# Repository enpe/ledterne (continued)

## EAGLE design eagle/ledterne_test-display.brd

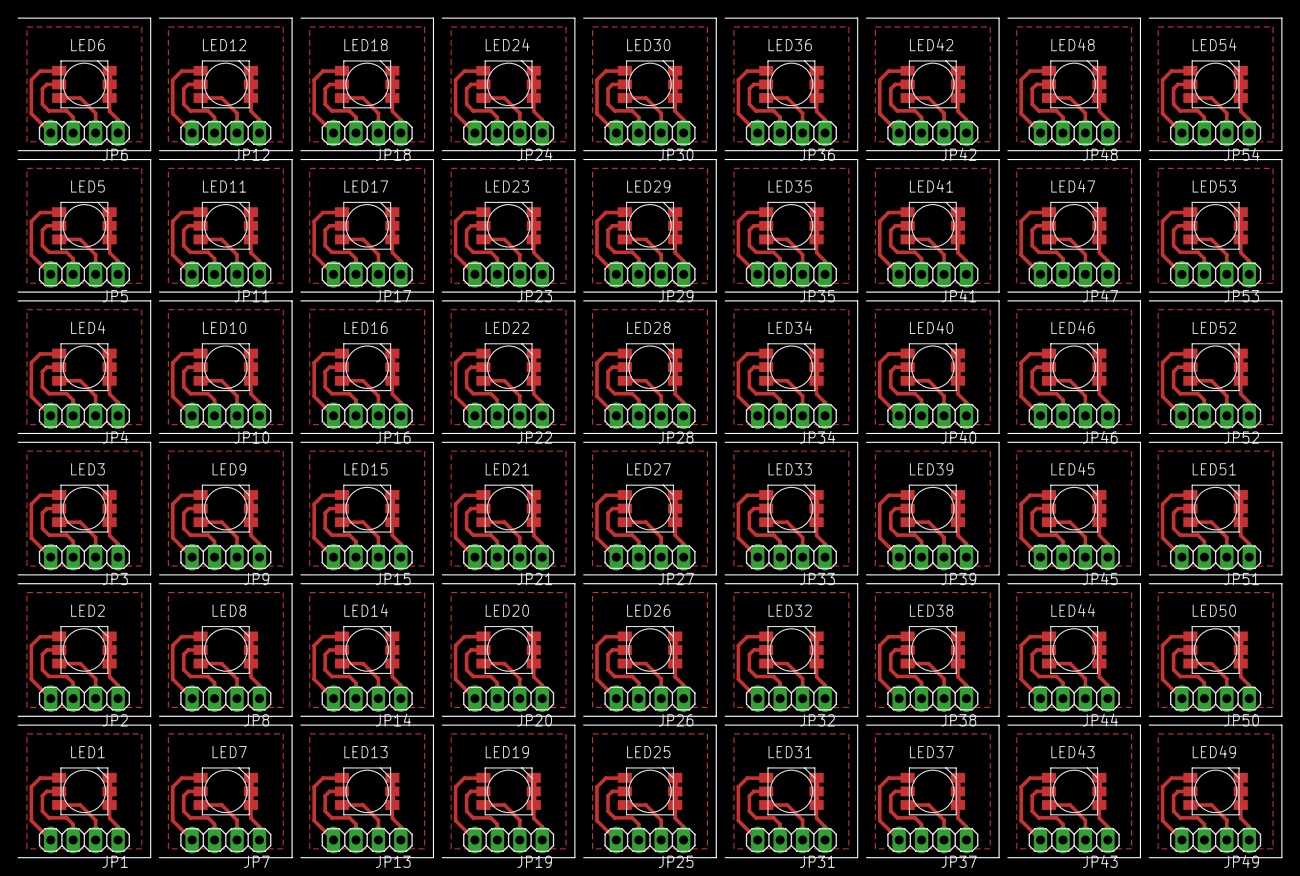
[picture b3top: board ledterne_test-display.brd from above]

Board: 2 copper layers, 143.0 x 95.0 mm, 108 parts (0 on the bottom side), 216 nets.

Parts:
JP1, JP2, JP3, JP4, JP5, JP6, JP7, JP8, JP9, JP10, JP11, JP12, JP13, JP14, JP15, JP16, JP17, JP18, JP19, JP20, JP21, JP22, JP23, JP24, JP25, JP26, JP27, JP28, JP29, JP30, JP31, JP32, JP33, JP34, JP35, JP36, JP37, JP38, JP39, JP40, JP41, JP42, JP43, JP44, JP45, JP46, JP47, JP48, JP49, JP50, JP51, JP52, JP53, JP54: 1X04
LED1, LED2, LED3, LED4, LED5, LED6, LED7, LED8, LED9, LED10, LED11, LED12, LED13, LED14, LED15, LED16, LED17, LED18, LED19, LED20, LED21, LED22, LED23, LED24, LED25, LED26, LED27, LED28, LED29, LED30, LED31, LED32, LED33, LED34, LED35, LED36, LED37, LED38, LED39, LED40, LED41, LED42, LED43, LED44, LED45, LED46, LED47, LED48, LED49, LED50, LED51, LED52, LED53, LED54: RGB-5252; SMD_5252

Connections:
GND: JP1.1, LED1.P1, LED1.P2, LED1.P3
GND1: JP2.1, LED2.P1, LED2.P2, LED2.P3
GND2: JP3.1, LED3.P1, LED3.P2, LED3.P3
GND3: JP4.1, LED4.P1, LED4.P2, LED4.P3
GND4: JP5.1, LED5.P1, LED5.P2, LED5.P3
GND5: JP6.1, LED6.P1, LED6.P2, LED6.P3
GND6: JP7.1, LED7.P1, LED7.P2, LED7.P3
GND7: JP8.1, LED8.P1, LED8.P2, LED8.P3
GND8: JP9.1, LED9.P1, LED9.P2, LED9.P3
GND9: JP10.1, LED10.P1, LED10.P2, LED10.P3
GND10: JP11.1, LED11.P1, LED11.P2, LED11.P3
GND11: JP12.1, LED12.P1, LED12.P2, LED12.P3
GND12: JP13.1, LED13.P1, LED13.P2, LED13.P3
GND13: JP14.1, LED14.P1, LED14.P2, LED14.P3
GND14: JP15.1, LED15.P1, LED15.P2, LED15.P3
GND15: JP16.1, LED16.P1, LED16.P2, LED16.P3
GND16: JP17.1, LED17.P1, LED17.P2, LED17.P3
GND17: JP18.1, LED18.P1, LED18.P2, LED18.P3
GND18: JP19.1, LED19.P1, LED19.P2, LED19.P3
GND19: JP20.1, LED20.P1, LED20.P2, LED20.P3
GND20: JP21.1, LED21.P1, LED21.P2, LED21.P3
GND21: JP22.1, LED22.P1, LED22.P2, LED22.P3
GND22: JP23.1, LED23.P1, LED23.P2, LED23.P3
GND23: JP24.1, LED24.P1, LED24.P2, LED24.P3
GND24: JP25.1, LED25.P1, LED25.P2, LED25.P3
GND25: JP26.1, LED26.P1, LED26.P2, LED26.P3
GND26: JP27.1, LED27.P1, LED27.P2, LED27.P3
GND27: JP28.1, LED28.P1, LED28.P2, LED28.P3
GND28: JP29.1, LED29.P1, LED29.P2, LED29.P3
GND29: JP30.1, LED30.P1, LED30.P2, LED30.P3
GND30: JP31.1, LED31.P1, LED31.P2, LED31.P3
GND31: JP32.1, LED32.P1, LED32.P2, LED32.P3
GND32: JP33.1, LED33.P1, LED33.P2, LED33.P3
GND33: JP34.1, LED34.P1, LED34.P2, LED34.P3
GND34: JP35.1, LED35.P1, LED35.P2, LED35.P3
GND35: JP36.1, LED36.P1, LED36.P2, LED36.P3
GND36: JP37.1, LED37.P1, LED37.P2, LED37.P3
GND37: JP38.1, LED38.P1, LED38.P2, LED38.P3
GND38: JP39.1, LED39.P1, LED39.P2, LED39.P3
GND39: JP40.1, LED40.P1, LED40.P2, LED40.P3
GND40: JP41.1, LED41.P1, LED41.P2, LED41.P3
GND41: JP42.1, LED42.P1, LED42.P2, LED42.P3
GND42: JP43.1, LED43.P1, LED43.P2, LED43.P3
GND43: JP44.1, LED44.P1, LED44.P2, LED44.P3
GND44: JP45.1, LED45.P1, LED45.P2, LED45.P3
GND45: JP46.1, LED46.P1, LED46.P2, LED46.P3
GND46: JP47.1, LED47.P1, LED47.P2, LED47.P3
GND47: JP48.1, LED48.P1, LED48.P2, LED48.P3
GND48: JP49.1, LED49.P1, LED49.P2, LED49.P3
GND49: JP50.1, LED50.P1, LED50.P2, LED50.P3
GND50: JP51.1, LED51.P1, LED51.P2, LED51.P3
GND51: JP52.1, LED52.P1, LED52.P2, LED52.P3
GND52: JP53.1, LED53.P1, LED53.P2, LED53.P3
GND53: JP54.1, LED54.P1, LED54.P2, LED54.P3
unnamed: JP2.2, LED2.P4
unnamed: JP2.3, LED2.P5
unnamed: JP1.2, LED1.P4
unnamed: JP1.3, LED1.P5
unnamed: JP1.4, LED1.P6
unnamed: JP2.4, LED2.P6
unnamed: JP3.2, LED3.P4
unnamed: JP3.3, LED3.P5
unnamed: JP3.4, LED3.P6
unnamed: JP4.2, LED4.P4
unnamed: JP4.3, LED4.P5
unnamed: JP4.4, LED4.P6
unnamed: JP5.2, LED5.P4
unnamed: JP5.3, LED5.P5
unnamed: JP5.4, LED5.P6
unnamed: JP6.2, LED6.P4
unnamed: JP6.3, LED6.P5
unnamed: JP6.4, LED6.P6
unnamed: JP7.2, LED7.P4
unnamed: JP7.3, LED7.P5
unnamed: JP7.4, LED7.P6
unnamed: JP8.2, LED8.P4
unnamed: JP8.3, LED8.P5
unnamed: JP8.4, LED8.P6
unnamed: JP9.2, LED9.P4
unnamed: JP9.3, LED9.P5
unnamed: JP9.4, LED9.P6
unnamed: JP10.2, LED10.P4
unnamed: JP10.3, LED10.P5
unnamed: JP10.4, LED10.P6
unnamed: JP11.2, LED11.P4
unnamed: JP11.3, LED11.P5
unnamed: JP11.4, LED11.P6
unnamed: JP12.2, LED12.P4
unnamed: JP12.3, LED12.P5
unnamed: JP12.4, LED12.P6
unnamed: JP13.2, LED13.P4
unnamed: JP13.3, LED13.P5
unnamed: JP13.4, LED13.P6
unnamed: JP14.2, LED14.P4
unnamed: JP14.3, LED14.P5
unnamed: JP14.4, LED14.P6
unnamed: JP15.2, LED15.P4
unnamed: JP15.3, LED15.P5
unnamed: JP15.4, LED15.P6
unnamed: JP16.2, LED16.P4
unnamed: JP16.3, LED16.P5
unnamed: JP16.4, LED16.P6
unnamed: JP17.2, LED17.P4
unnamed: JP17.3, LED17.P5
unnamed: JP17.4, LED17.P6
unnamed: JP18.2, LED18.P4
unnamed: JP18.3, LED18.P5
unnamed: JP18.4, LED18.P6
unnamed: JP19.2, LED19.P4
unnamed: JP19.3, LED19.P5
unnamed: JP19.4, LED19.P6
unnamed: JP20.2, LED20.P4
unnamed: JP20.3, LED20.P5
unnamed: JP20.4, LED20.P6
unnamed: JP21.2, LED21.P4
unnamed: JP21.3, LED21.P5
unnamed: JP21.4, LED21.P6
unnamed: JP22.2, LED22.P4
unnamed: JP22.3, LED22.P5
unnamed: JP22.4, LED22.P6
unnamed: JP23.2, LED23.P4
unnamed: JP23.3, LED23.P5
unnamed: JP23.4, LED23.P6
unnamed: JP24.2, LED24.P4
unnamed: JP24.3, LED24.P5
unnamed: JP24.4, LED24.P6
unnamed: JP25.2, LED25.P4
unnamed: JP25.3, LED25.P5
unnamed: JP25.4, LED25.P6
unnamed: JP26.2, LED26.P4
unnamed: JP26.3, LED26.P5
unnamed: JP26.4, LED26.P6
unnamed: JP27.2, LED27.P4
unnamed: JP27.3, LED27.P5
unnamed: JP27.4, LED27.P6
unnamed: JP28.2, LED28.P4
unnamed: JP28.3, LED28.P5
unnamed: JP28.4, LED28.P6
unnamed: JP29.2, LED29.P4
unnamed: JP29.3, LED29.P5
unnamed: JP29.4, LED29.P6
unnamed: JP30.2, LED30.P4
unnamed: JP30.3, LED30.P5
unnamed: JP30.4, LED30.P6
unnamed: JP31.2, LED31.P4
unnamed: JP31.3, LED31.P5
unnamed: JP31.4, LED31.P6
unnamed: JP32.2, LED32.P4
unnamed: JP32.3, LED32.P5
unnamed: JP32.4, LED32.P6
unnamed: JP33.2, LED33.P4
unnamed: JP33.3, LED33.P5
unnamed: JP33.4, LED33.P6
unnamed: JP34.2, LED34.P4
unnamed: JP34.3, LED34.P5
unnamed: JP34.4, LED34.P6
unnamed: JP35.2, LED35.P4
unnamed: JP35.3, LED35.P5
unnamed: JP35.4, LED35.P6
unnamed: JP36.2, LED36.P4
unnamed: JP36.3, LED36.P5
unnamed: JP36.4, LED36.P6
unnamed: JP37.2, LED37.P4
unnamed: JP37.3, LED37.P5
unnamed: JP37.4, LED37.P6
unnamed: JP38.2, LED38.P4
unnamed: JP38.3, LED38.P5
unnamed: JP38.4, LED38.P6
unnamed: JP39.2, LED39.P4
unnamed: JP39.3, LED39.P5
unnamed: JP39.4, LED39.P6
unnamed: JP40.2, LED40.P4
unnamed: JP40.3, LED40.P5
unnamed: JP40.4, LED40.P6
unnamed: JP41.2, LED41.P4
unnamed: JP41.3, LED41.P5
unnamed: JP41.4, LED41.P6
unnamed: JP42.2, LED42.P4
unnamed: JP42.3, LED42.P5
unnamed: JP42.4, LED42.P6
unnamed: JP43.2, LED43.P4
unnamed: JP43.3, LED43.P5
unnamed: JP43.4, LED43.P6
unnamed: JP44.2, LED44.P4
unnamed: JP44.3, LED44.P5
unnamed: JP44.4, LED44.P6
unnamed: JP45.2, LED45.P4
unnamed: JP45.3, LED45.P5
unnamed: JP45.4, LED45.P6
unnamed: JP46.2, LED46.P4
unnamed: JP46.3, LED46.P5
unnamed: JP46.4, LED46.P6
unnamed: JP47.2, LED47.P4
unnamed: JP47.3, LED47.P5
unnamed: JP47.4, LED47.P6
unnamed: JP48.2, LED48.P4
unnamed: JP48.3, LED48.P5
unnamed: JP48.4, LED48.P6
unnamed: JP49.2, LED49.P4
unnamed: JP49.3, LED49.P5
unnamed: JP49.4, LED49.P6
unnamed: JP50.2, LED50.P4
unnamed: JP50.3, LED50.P5
unnamed: JP50.4, LED50.P6
unnamed: JP51.2, LED51.P4
unnamed: JP51.3, LED51.P5
unnamed: JP51.4, LED51.P6
unnamed: JP52.2, LED52.P4
unnamed: JP52.3, LED52.P5
unnamed: JP52.4, LED52.P6
unnamed: JP53.2, LED53.P4
unnamed: JP53.3, LED53.P5
unnamed: JP53.4, LED53.P6
unnamed: JP54.2, LED54.P4
unnamed: JP54.3, LED54.P5
unnamed: JP54.4, LED54.P6

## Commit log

2015-07-12 Added a README-file.
2015-07-13 Add some documentation
2015-07-13 Replace ramp up/down hack
    Instead of building the up/down motion into the lookup table,
    the animation is now completely done in the function that
    controls the LED brightness values.
2015-07-13 Fix typo in comments
2015-07-13 Replace busy wait with interrupt-driven frame tick
    Every frame tick advances the color animation one step.
    The 16-bit timer that was previously used for the PWM is now
    replaced by an 8-bit timer. The 16-bit timer is instead used for
    generating the frame tick. This was necessary because the
    required compare values for the frame tick timer would not fit
    into an 8-bit register.
2015-07-18 Add support for 4 more RGB LED outputs
    All 5 LEDs currently show the same colors even though separate
    control of every single LED is already possible in the code.
2015-07-18 Add some TODOs
2015-07-19 Make ramp functions reusable
    The maximum value is not hard-coded anymore.
    The functions also reside in a separate file now. This will
    hopefully prevent clutter in the main program file.
2015-07-19 Refactor up/down ramp animation into object function
    This releases the caller from handling internal implementation
    details (in this case: the variable that keeps track of the
    current direction).
2015-07-19 Refactor current color blending into animation object
2015-07-19 Replace explicit setting of single pixels with loops
2015-07-19 Refactor color blending animation
    Instead of repeatedly being called in the main program, this is
    now a standalone animation block that sets the desired LED
    colors all by itself.
    This should make it easier to add similar animations blocks
    without being forced to repeating the same boilerplate code in
    the main program over and over again.
2015-07-19 Add a Knight-Rider-style animation program
2015-07-19 Let programs signal when they have completed an iteration
2015-07-19 Add mechanism for playing multiple programs in a defined order
2015-07-19 Use function pointers for animation destruction and execution
    This saves us dealing with switches for the animation program
    type all the time.
    It works but still does not look quite right (generates compiler
    warnings). This might need fixing.
2015-07-19 Remove Knight Rider's hard-coded fade intensities
    The values are now computed relative to the given maximum LED
    intensity. The result should still be the same as before.
2015-07-19 Signal completion of a full up/down ramp animation
2015-07-19 Add a colored conveyor belt animation program
2015-07-19 Fix colliding #defines
2015-07-19 Remove superfluous parameter from animation program constructor
    The maximum LED brightness is known inside the animations
    programs anyway. No need to pass it as parameter. The other
    animation programs do not do this either.
2015-07-22 Add live-recording of the current animations
2015-07-22 Simplify code by using the rampUp function
2015-07-22 Signal completion of a full rampUp animation
2015-07-22 Some more putting rampUp to good use
2015-07-22 Slow down Knight Rider
    The animation will now update on every second frame only. It
    looked shitty previously.
2015-07-27 Add some LED information
2015-08-04 Add Eagle library for our types of RGB LEDs
2015-08-06 - Added rough sketches of the schematics and board layout.
2015-08-07 - Added possible routing (one layer only).
2015-08-08 Clean up the schematic a little bit
    Making everything a bit more compact and using less wires.
2015-08-08 Assign net names to the LED inputs
2015-08-08 Update routing to be more compact
2015-08-09 Change driver board to match the display board size
    5 display boards will be arranged in an upright position forming
    a cylinder with a pentagonal base. The driver board is a pentagon
    that then acts as sort of lid for this cylinder.
2015-08-09 Add connectors to the driver board
    These connectors will allow the display boards to attach to the
    driver board.
    Note that this is just a very rough sketch for demonstrating the
    basic idea. The exact placement and type of connectors will have
    to be fine-tuned later.
2015-08-17 Add alternative plan for PWM optimization as note
2015-08-23 Add some pictures for documentation of the test display
2015-08-24 Add some more test display pictures
    Also rename the existing ones to use two digits for numbering.
2015-08-30 Update TODO list
2015-08-31 Add EAGLE layout for the test display board
    This is basically a breakout board for the SMD LEDs.
2015-08-31 Update TODO list with some programming stuff
2015-10-02 Add script for generating the pentagon driver board
    This is useful for playing with different sizes of the board and
    placing of the parts.
2015-10-02 Add option to supply board's side length instead of radius
2015-10-03 Clean up dialog layout a little
2015-10-03 Add option to keep the dialog open after execution
2015-10-03 Add library for pinheads with round pads.
2015-10-03 Start connecting the components of the driver.
2015-10-03 Change attributes of source files (chmod -x)
2015-10-03 Add connector for supply voltage
2015-10-03 Increase pinhead's diameter for easier soldering/drilling
2015-10-04 Alternative routing for driver board
2015-10-04 Add ground plane on bottom side
2015-10-04 Place ISP solder pads on the board
2015-10-04 Replace ISP connector with solder pads
2015-10-04 Slightly shrink the ISP solder pads
2015-10-04 Move MOSI solder pad away from board's corner
    We might need this place for an additional mount.
2015-10-05 Add capacitor values
2015-10-06 Clean up the schematic a little
2015-10-08 Increase driver board's side length to 16 mm
2015-10-08 Replace ISP solder pads with through-hole pins
2015-10-08 Add construction idea for the battery holder and add links to other DIY battery holder projects.
2015-10-08 Switch to a slightly larger capacitor package
2015-10-08 Finally fix the routing again
2015-10-09 Increase width of display board's outline
2015-10-09 Adjust placement of display board's connector
    The connector is now placed in such way that, when connecting
    the display board with the driver board by using a right-angle
    pin header, the display board's borders are flush with the
    driver board's borders.
2015-10-09 Add ground plane on display board
2015-10-09 Limit diameter of display board's drills
2015-10-10 Add drills for attaching mounts to the driver board
2015-10-10 Add driver board's name and version as text labels
2015-10-10 Guard ISP pin connectors against routes on bottom layer
    We want to place these connectors on the board's bottom layer,
    so we do not want any bottom routes to be connected. Only
    soldering on the top layer is allowed here and we do not have
    connected vias available.
2015-10-10 Slightly increase distance between ISP solder pads and other pads
2015-10-10 Move driver's mount drills slightly away from borders
2015-10-10 Limit diameter of driver board's drills
2015-10-11 Add layout versions for printing a complete Eurocard board
    The display board also has Yo's entirely unrelated layout on the
    same Eurocard.
2015-10-21 Change output pins in software to match current board layout
2015-10-21 Add program test to check if all displays are functional.
2015-10-25 Match TestDisplays's function naming scheme to other programs
2015-10-26 Add switch for displaying memory usage in `make stats`
2015-10-26 Add ATmega8A datasheet
    Since that is the microcontroller we are using in the final
    LEDterne.
2015-10-28 Fix conveyor animation
    The rotation and fading speeds are now adjusted so that a full
    cycle of the animation blends seemlessly in time.
2015-10-28 Add alternative to incremental ramp function
    Instead, compute the required triangle function analytically
    for a given frame index.
2015-11-07 Properly handle periodicity
2015-11-07 Add back the cycling through the colors
2015-11-07 Remove old ramp-based version
2015-11-07 Clean up a little
2015-11-07 Add back the animations that got lost in the merge
    Except for the display test. We do not want that to play by
    default. ;)
2015-11-09 Slow down the animation clock instead of skipping frames
    Animations that need to run at lower frame rates can now simply
    adjust the animation clock accordingly instead of slowing the
    animation down by internally skipping frames.
    This also makes it possible to increase the frame rate, of
    course.
2015-11-11 Add flickering animation to simulate a candle
2015-11-11 Let every LED flicker independently
2015-11-11 Add a probabilistic termination criteria to the candle flicker.
